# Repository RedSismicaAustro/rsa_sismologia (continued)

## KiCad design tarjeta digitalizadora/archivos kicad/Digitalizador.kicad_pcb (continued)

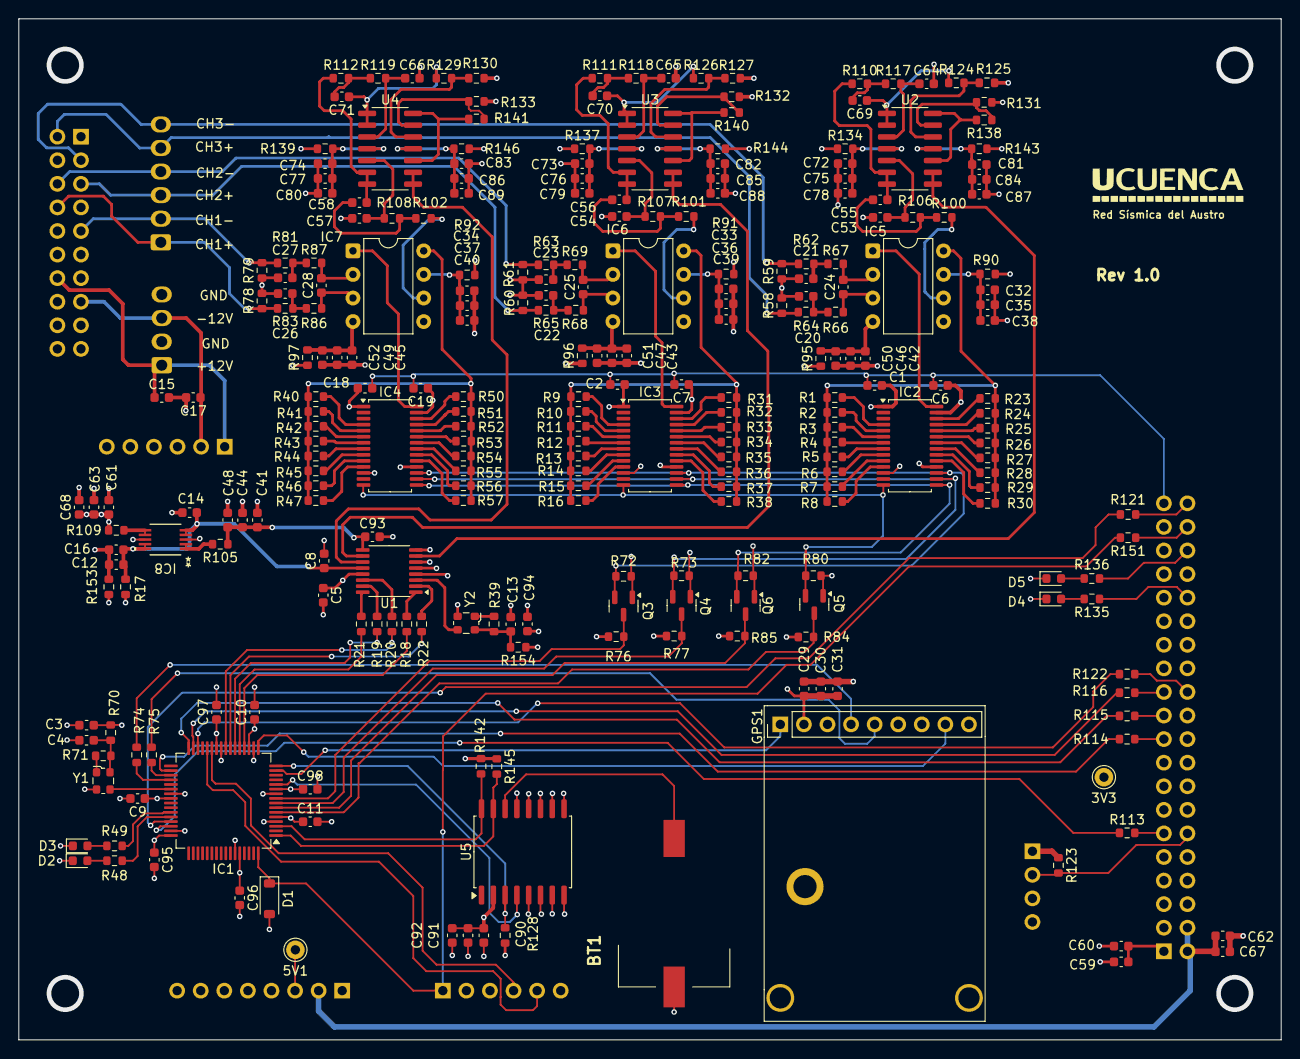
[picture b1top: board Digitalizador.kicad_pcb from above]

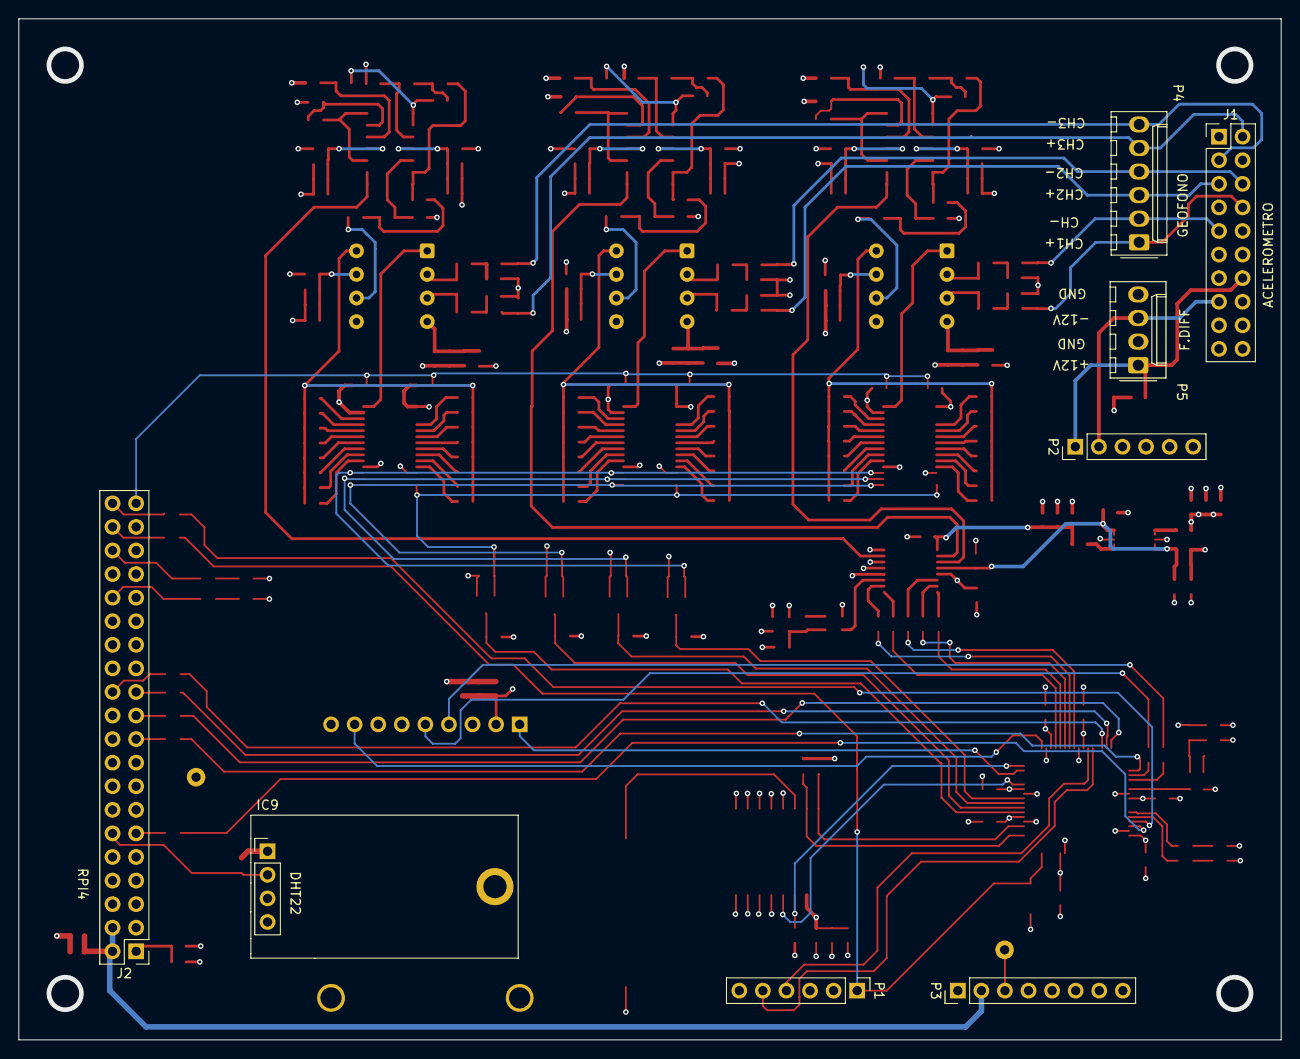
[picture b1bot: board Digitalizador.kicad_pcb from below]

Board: 4 copper layers, 136.0 x 110.0 mm, 274 parts (8 on the bottom side), 193 nets.

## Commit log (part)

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2025-05-20 Inicial
    Todo el inicio
2025-05-28 Respaldo intermedio
    Se ha intentado corregir los cuelgues por el manejo de los gráficos, cosa que ha salido infructuosa. De momento se cambia de tema, vamos por los acelerogramas.
2025-06-13 Respaldo por error en git al 13 de junio
    Error garrafal en el manejo del repositorio borrando la rama extraer sin hacer un commit. Recuperada la información pero se pierde los últimos 3 días, no de los últimos 15 como en un principio. Vamos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
2025-06-13 Librería extraer.
    Actualización de la librería extraer_() por extraer() en metodos_rsa, aquí se cambia la extracción por evento, a una extracción de un grupo de eventos de manera de evitar los cuelgues por la exesiva 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
2025-06-15 Depuración de proyecto
    Se han borrado métodos antiguos de extraer y borrado los programas de pruebas para bajar el tamaño y organizar adecuadamente el repositorio.
2025-06-15 Detalles de extraer, barra de progreso
    Se ha colocado una barra de progreso al momento de extraer los sismos. Adicionalmente se ha corregido un error en los archivos de 250 MPS y 20 bits de representación para que se ajuste a 16 bits para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
2025-06-16 Corrección de reportes semanales
    Se achica los tamaños del reporte para la facultad.
2025-06-17 Modificación de programas para registro de otras redes.
    La página del IGEPN ha cambiado y ya no corresponde el formato para la inserción de datos, por lo que se ha procedido a actualizarlos. Además, se corrigió los errores generados en los reportes catálo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
2025-06-21 temporal
    Me paso al main para procesar un evento fuerte.
2025-06-24 Cambios en extraer relevantes.
    Cambios por el evento del 21 de junio. Al extraer muchos eventos, genera confusión, por lo que se hace una rutina para poder marcar los extraídos. Además se genera código para verificar que eventos a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
2025-06-25 Compatibilidad para trabajar en otra computadora.
    Se han modificado archivos de lanzamiento en la computadora todo en uno
2025-06-26 Emparejamiento con los otros desarrollos
    Hay cambios principalmente en los .bat y la inserción de estaciones , quizá no haga la grande.
2025-06-27 Actualizaciones fuera de sincronía.
    Algo se ha ejecutado mal. Las correcciones hechas se han perdido o actualizado en versiones no funcionales. Aparentemente no tal complejas pero errores ya subsanados han vuelto a aparecer por la actu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
2025-06-27 Modificaciones en el bat
    No logro comprender porqué se sigue alterando este lanzador.
2025-06-28 Comit del viernes 27 para ir a casa
    Algunos procesos que se encontraron desactualizados de procesamiento, también se está pensando en una mejor manera de ingresar información de otras redes a la estructura de datos.
2025-06-30 A trabajo el 30 de junio
    Actualización para trabajar en oficina el 30 de junio. Pequeños cambios en scripts de caudales y librerías. Hay que unificar todas las variables que contengan números de estaciones, unas están como c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
2025-07-07 Desde casa 7/7/2024
    Se hace correcciones en el método guardar información diaria que no está modificando los cambios de eventos. Se empieza un script para realizar el cambio del formato de año de 2 a 4 dígitos.
2025-07-12 Salida a casa 11 de julio
    Se está trabajando en el paso del sistema a formato de año de cuatro dígitos.
2025-07-14 A trabajo
    Casi no hay cambios.
2025-07-15 Casa, martes 15 de julio
    Sigo con la migración.
2025-07-16 A casa 15 de julio
    Se continúa con el cambio de formato de año en 4 dígitos.
2025-07-19 Salida a casa 18 de julio
    Se está trabajando en el procesamiento, hay muchos errores por el cambio de formato a años de cuatro cifras.
2025-07-21 A trabajo 21 de julio
    Trabajo hecho en casa, procesamiento
2025-07-22 A trabajo 22 de julio
    Trabajando en el calculo de los caudales. Hay que ir con cuidado para no dañar los archivos de registro.
2025-08-05 A trabajo 5 de agosto.
    Integración de los programas en uno solo.
2025-08-05 Últimos cambios viernes 1
    Correcciones sobre los reportes, especialmente reporte de períodos.
2025-08-09 A casa 8 de agosto
    Menu
2025-08-16 Actualización 15 de agosto.
    Corrección de errores de los reportes actualizado al 15 de agosto.
2025-08-19 18 de agosto desde casa
    Se corrigieron errores de extracción y generación del .sis para procesamiento.
2025-08-19 19 de agosto en la mañana
    Corregido errores generados por el paso de 2 a 4 dígitos en el programa de caudales.
2025-09-01 A trabajo al 1 de septiembre
    Cambio drástico en el programa de procesamiento.
2025-09-01 Cambios automático
    Cambios realizados en automático para que corra adecuadamente con el nuevo formato de día con cuatro dígitos.
2025-09-02 desde casa
    Programa para árbol e directorios
2025-09-03 Desde casa 3 de septiembre
    Programa para Milton
2025-09-04 desde trabajo 3 de agosto
    Cambios en librerías y programa nuevo de consultas.
2025-09-04 desde casa 4 de septiembre
    Programa de consulta de Milton.
2025-09-20 A casa 19 de septiembre
    Trabajos para arreglar el programa integrado. Trabajando sobre los widgets graficos
2025-09-22 desde casa 21 de septiembre
    Arreglos de programa principal
2025-09-27 A casa 26 de septiembre
    Arreglado varios programas e integrado al procesamiento integrado.
2025-09-27 de casa sábado 27
    Corrección de inserción de otras redes al catalogo
2025-09-30 A casa 29 de septiembre
    Arreglar reportes de sismos en el mismo minuto
2025-09-30 desde casa 30 de septiembre
    Sigo arreglando lo de los reportes
2025-09-30 Últimos cambios de septiembre
    Recuperando reportes de periodos
2025-10-03 A casa 3 de octubre
    Varios temas sobre reportes y programa integrado
2025-10-07 Desde trabajo 6 de octubre
    Corrección para reporte acumulado para reporte semanal.
2025-10-07 desde casa 6 de octubre 2
    Arreglo de automatico
2025-10-08 A casa 7de octurbre
    Cambio en automático para no ocupar mucho tiempo en procesamiento.
2025-10-08 En trabajo 8 de agosto
    Commit para poder regresarme a la versión anterior de automático, pues no funciona adecuadamente y poder procesar.
2025-10-10 en casa 10 de octubre
    He montado en automatico otro archivo por error, esta es la recuperación del original.
2025-10-14 A trabajo 13 de octubre
    Corrección de acelerógrafo
2025-10-22 desde casa 22 de octubre
    De apuro
2025-10-25 A casa 24 de octubre
    Actualización de los archivos de procesamiento integrado.
2025-10-27 Desde casa 27 de octubre
    Algunos cambios de ultima hora en el programa integrado
2025-10-28 a casa 27 de octubre
    Cambios generales
2025-10-29 Métodos gráficos
    Cambio de paradigma en la librería de métodos gráficos. Se cambia del uso indiscriminado de banderas a modos. 6 modos.
2025-11-05 A trabajo 4 de noviembre
    Arreglos en automático y en los reportes.
2025-11-18 A casa 17 de noviembre
    Se sigue trabajando en el interfaz y los programas de inciciación.
2025-11-21 A casa 21 de noviembre
    Programa nueva para leer del puerto serial, pero nada mas.
2025-11-26 A casa 25 de noviembre
    Arreglo del programa principal, principalmente procesamiento para que trabaje dentro de la ventana y no genere una ventana independiente. Trabajo en desarrollo
2025-11-30 A oficina 30 de noviembre
    Se crea programa para analizar directorios
2025-12-07 a casa 7 de diciembre
    Correcciones de lo reportes para informes
2025-12-13 a casa 12 de diciembre
    Trabajos con SP 32, tarjeta Sebastian
2025-12-20 Temporal 20 12 2025 1
    Para ejecutar en oficina
2025-12-23 A oficina 23 de diciembre
    Cambios realizados en el programa para el manejo de los evt con problemas de reseteo de la fecha.
2025-12-25 A casa 25 de diciembre
    QUiza no se dañe
2025-12-25 Hacia oficina 25 de diciembre
    Cambios en la emisión de reportes.
2026-01-17 A casa 17 de enero
    Errores enprocesamiento
2026-02-28 Migración a un adecuado contexto de capas de programación.
    Se ha empezado con la migración hacia un modelo de programación por capas para corregir los errores de concepto de programación. Están los archivos me den la raíz donde se establece los programas enc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
2026-03-07 Mejora a arquitectura por capas
    Se divide la librería metodos_rsa.py en varios librerías rsa-dominios.py, rsa<-io.py rsa<-parocesamiento.py quedando pendiente otros métodos en la librería original.
2026-03-11 Migraciones y correcciones
    Se sigue con la etapa de migraciones de librerías para estructurar el modelo de capas. Además se corrige el error de automático para que recoja todos los archivos binarios de R:
2026-03-12 A oficina 12 de marzo
    Trabajo en casa sobre los reportes en pdf en los periodos.
2026-03-13 Corrección de error.
    Error en la librería rsa_procesamiento, concretamente en el método lectura_rsa.
2026-03-15 Corrección de error en mapa
    Se sigue con la corrección del error en el mapa y el procesamiento de los eventos. Se ha creado la rama para el efecto.
2026-03-21 A casa 20 de marzo
    SE sigue con la corrección de los datos de procesamiento, se ha trabajado con el programa de procesamiento y la lectura y gestión de los archivos fast. Hay un error en la emisión de los reportes pdf.
2026-03-22 interno 22 de marzo
    Tratando de arreglar el error de detección de archivos_fast
2026-03-23 A trabajo 23 de marzo
    Se sigue trabajando con las correcciones de fast
2026-03-26 A casa 25 de marzo
    Corrección de inserción EVT.
2026-03-30 A trabajo 29 de marzo
    Creado un programa para corregir errores de los caudales y niveles
2026-05-14 Actualización de archivos.
    No he programado hace algún tiempo y he empezada a trabajar con el SP32 con las cajas de medición.
2026-05-15 Actualizaciones de librerias.
    Librerías Stellaris comentadas
2026-05-28 A casa, 27 de mayo
    Cambios que no veo relevantes
2026-05-31 Desde casa 30 de mayo.
    He arreglado la versión de acelerógrafo para que no una parcialmente y siempre una todo. Voy a trabajar de archivos fast y necesito el punto para que no haya problemas. Voy a usar DEEPSEEK.
2026-05-31 Desde casa 31 de mayo
    Arreglado acelerografo y automático para subir la información sismica.
2026-05-31 desde oficina 31 de mayo
    No he realizado el commit adecuadamente
2026-06-04 Mejora flujo de corrección y exportación EVT
    - Separa guardar eventos de salir de la aplicación.
    - Exporta todos los EVT recalculados, no solo los marcados como sismo.
    - Ajusta la fecha de modificación de cada EVT exportado a su fecha corregida.
    - Unifica calibración y asignación contra catálogo.
    - Recalcula siempre desde la referencia original.
    - Fuerza diferencia 0 para el EVT usado como referencia.
2026-06-05 Mejorar procesamiento y reconstrucción de archivos EVT
    - Renombra funciones y variables para hacer más claro el flujo de inserción de EVT.
    - Agrega manejo de errores por archivo durante el procesamiento por lotes.
    - Permite cargar listas CSV extrayendo rutas EVT válidas.
    - Actualiza la carga de subdirectorios según el año seleccionado.
    - Agrega preclasificación de carpetas posteriores al año 2000 hacia un destino elegido.
    - Implementa detección de posibles reseteos EVT por cambios de serie.
2026-06-06 Corrección de scripts de módulos externos RSA
    Se agrega un punto de control inicial para la revisión de scripts ubicados en módulos externos de la estructura del proyecto RSA.
    Scripts incluidos para corrección posterior:
    - acelerografo_v02.py
    - automatico V2.py
    - caudales_filtraciones.py
    - Insercion de estaciones EVT.py
2026-06-06 Integra consolidacion MSEED y limpia flujos analogico/digital
    - Renombra los programas principales a acelerografo.py y automatico.py.
    - Elimina versiones antiguas de acelerografo y automatico.
    - Restaura automatico.py como flujo analogico puro desde R:.
    - Agrega consolidacion_mseed.py como flujo integrado analogico + digital.
    - Separa la configuracion digital para evitar que la etapa analogica altere HAB_CANAL/CODIGO.
    - Procesa estaciones digitales desde Datos Estaciones usando datos/digitales.csv.
2026-06-11 Programas nuevos y contextos
    Se ha realizado un programa nuevo para controlar las versiones de los archivos del directorio DIA (o cualquier directorio).
    Se ha generado un archivo de contexto para el programa principal del procesamiento de datos.
